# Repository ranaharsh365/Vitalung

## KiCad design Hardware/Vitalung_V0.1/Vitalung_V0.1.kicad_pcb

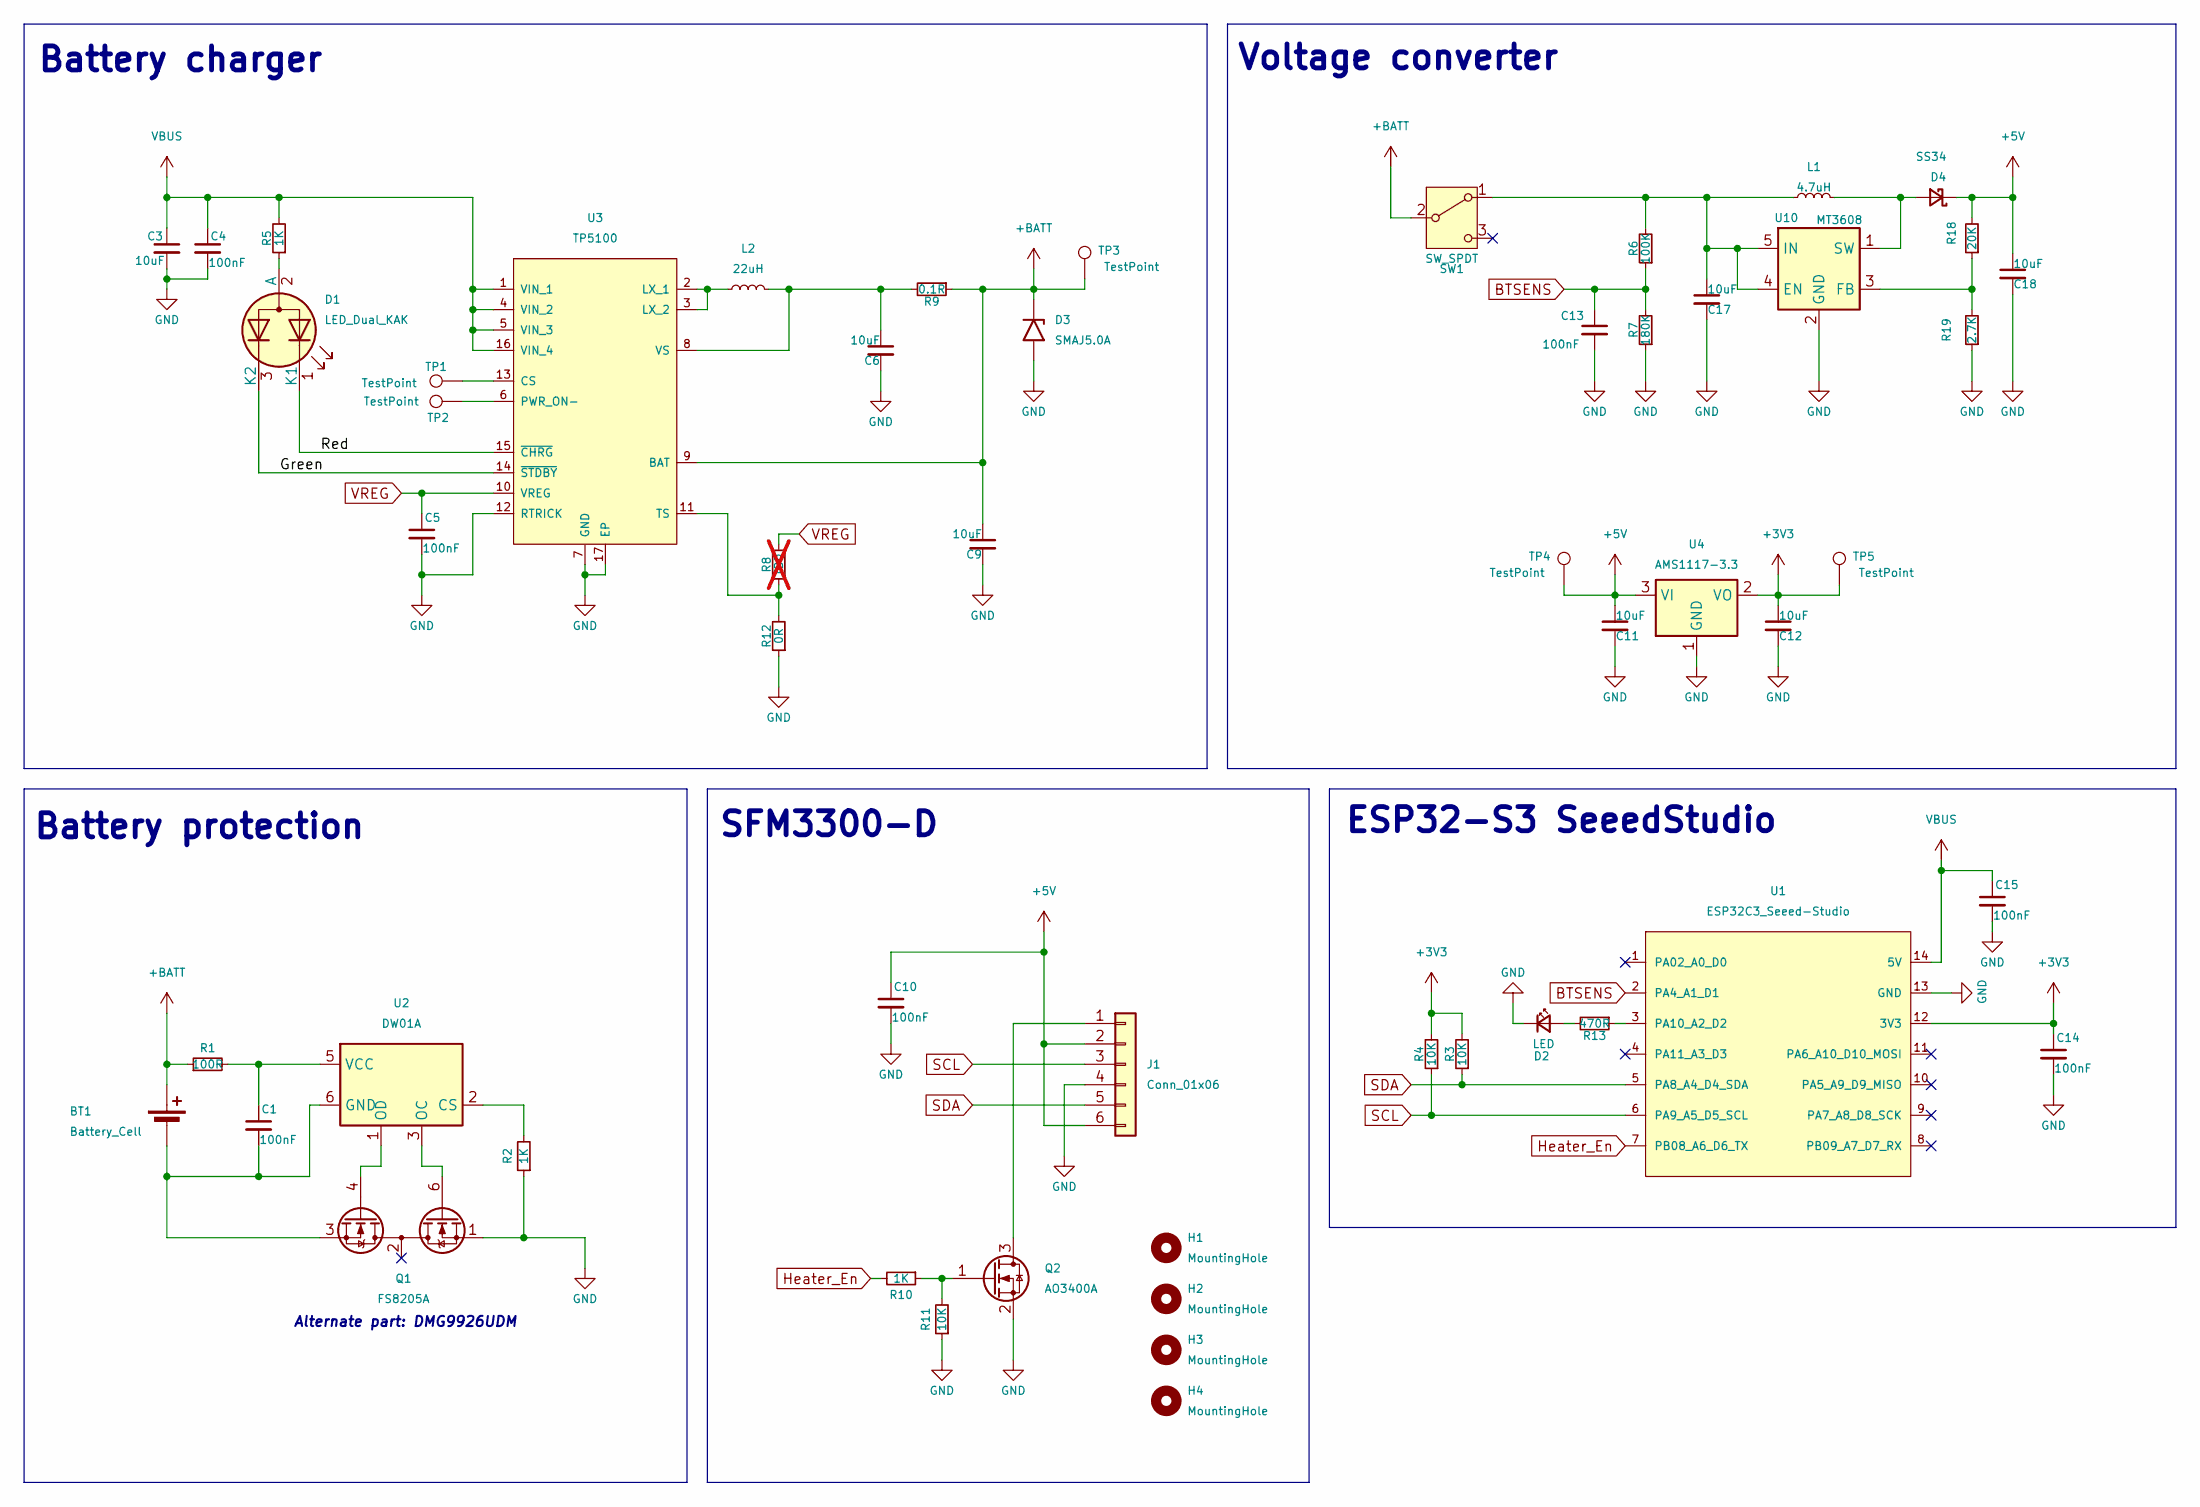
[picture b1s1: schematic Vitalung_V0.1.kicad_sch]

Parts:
BT1: Battery_Cell; BatteryHolder_MPD_BH-18650-PC2
C1, C4, C5, C10, C13, C14, C15: 100nF; C_0603_1608Metric_Pad1.08x0.95mm_HandSolder
C3, C6, C9, C11, C12, C17, C18: 10uF; C_0805_2012Metric_Pad1.18x1.45mm_HandSolder; JLCPCB Part # C96446
D1: LED_Dual_KAK; LED_D3.0mm-3
D2: LED; LED_D3.0mm
D3: SMAJ5.0A; D_SMA
D4: SS34; D_SMA; JLCPCB Part # C8678
H1, H2, H3, H4: MountingHole; MountingHole_2.2mm_M2
J1: Conn_01x06; PinHeader_1x06_P2.54mm_Vertical
L1: 4.7uH; L_Abracon_ASPI-0425; MFR Part no. FXL0420-4R7-M; JLCPCB Part # C167208
L2: 22uH; L_Abracon_ASPI-0630LR
Q1: FS8205A; SOT-23-6
Q2: AO3400A; SOT-23
R1: 100R; R_0603_1608Metric_Pad0.98x0.95mm_HandSolder
R2, R10: 1K; R_0603_1608Metric_Pad0.98x0.95mm_HandSolder
R3, R4: 10K; R_0603_1608Metric_Pad0.98x0.95mm_HandSolder; JLCPCB Part # C4184
R5: 1K; R_0603_1608Metric_Pad0.98x0.95mm_HandSolder; JLCPCB Part # C4184
R6: 100K; R_0603_1608Metric_Pad0.98x0.95mm_HandSolder; JLCPCB Part # C25803
R7: 180K; R_0603_1608Metric_Pad0.98x0.95mm_HandSolder; JLCPCB Part # C123419
R8: TBD; R_0603_1608Metric_Pad0.98x0.95mm_HandSolder; JLCPCB Part # C4184; not fitted
R9: 0.1R; R_0805_2012Metric_Pad1.20x1.40mm_HandSolder; JLCPCB Part # C4184
R11: 10K; R_0603_1608Metric_Pad0.98x0.95mm_HandSolder
R12: 0R; R_0603_1608Metric_Pad0.98x0.95mm_HandSolder; JLCPCB Part # C4184
R13: 470R; R_0603_1608Metric_Pad0.98x0.95mm_HandSolder; JLCPCB Part # C4184
R18: 20K; R_0603_1608Metric_Pad0.98x0.95mm_HandSolder; JLCPCB Part # C4184
R19: 2.7K; R_0603_1608Metric_Pad0.98x0.95mm_HandSolder; JLCPCB Part # C13167
SW1: SW_SPDT; SW_Slide_SPDT_Angled_CK_OS102011MA1Q; JLCPCB Part # C2939726
TP1, TP2, TP3, TP4, TP5: TestPoint; TestPoint_Pad_D1.0mm
U1: ESP32C3_Seeed-Studio; ESP32C3-SeedStudio-SMD-2.54-21X17.8MM
U2: DW01A; SOT-23-6
U3: TP5100; QFN-16-1EP_4x4mm_P0.65mm_EP2.1x2.1mm
U4: AMS1117-3.3; SOT-223-3_TabPin2
U10: MT3608; SOT-23-6; JLCPCB Part # C84817

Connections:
+3V3: C12.1, C14.1, R3.2, R4.2, TP5.1, U1.12 (3V3), U4.2 (VO)
+5V: C10.1, C11.1, C18.1, D4.1 (K), J1.2, J1.6, R18.2, TP4.1, U4.3 (VI)
+BATT: BT1.1 (+), C9.1, D3.1 (A1), R1.1, R9.1, SW1.2 (B), TP3.1, U3.9 (BAT)
/Green: D1.3 (K2), U3.14 (~STDBY)
/Red: D1.1 (K1), U3.15 (~CHRG)
BTSENS: C13.1, R6.1, R7.2, U1.2 (PA4_A1_D1)
GND: C3.2, C4.2, C5.2, C6.2, C9.2, C10.2, C11.2, C12.2, C13.2, C14.2, C15.2, C17.2, C18.2, D2.1 (K), D3.2 (A2), J1.4, Q1.1 (D1), Q2.2 (S), R2.1, R7.1, R11.1, R12.1, R19.1, U1.13 (GND), U3.7 (GND), U3.12 (RTRICK), U3.17 (EP), U4.1 (GND), U10.2 (GND)
Heater_En: R10.2, U1.7 (PB08_A6_D6_TX)
unnamed: BT1.2 (-), C1.2, Q1.3 (S2), U2.6 (GND)
unnamed: D1.2 (A), R5.1
unnamed: D2.2 (A), R13.2
unnamed: D4.2 (A), L1.2, U10.1 (SW)
unnamed: J1.1, Q2.3 (D)
unnamed: Q1.6 (G1), U2.3 (OC)
unnamed: Q1.4 (G2), U2.1 (OD)
unnamed: Q2.1 (G), R10.1, R11.2
unnamed: C17.1, L1.1, R6.2, SW1.1 (A), U10.4 (EN), U10.5 (IN)
unnamed: R13.1, U1.3 (PA10_A2_D2)
unnamed: R2.2, U2.2 (CS)
unnamed: C1.1, R1.2, U2.5 (VCC)
unnamed: TP1.1, U3.13 (CS)
unnamed: L2.1, U3.2 (LX_1), U3.3 (LX_2)
unnamed: TP2.1, U3.6 (PWR_ON-)
unnamed: R8.1, R12.2, U3.11 (TS)
unnamed: C6.1, L2.2, R9.2, U3.8 (VS)
unnamed: R18.1, R19.2, U10.3 (FB)
SCL: J1.3, R4.1, U1.6 (PA9_A5_D5_SCL)
SDA: J1.5, R3.1, U1.5 (PA8_A4_D4_SDA)
VBUS: C3.1, C4.1, C15.1, R5.2, U1.14 (5V), U3.1 (VIN_1), U3.4 (VIN_2), U3.5 (VIN_3), U3.16 (VIN_4)
VREG: C5.1, R8.2, U3.10 (VREG)

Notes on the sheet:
ESP32-S3 SeeedStudio
SFM3300-D
Battery charger
Battery protection
Voltage converter
Alternate part: DMG9926UDM

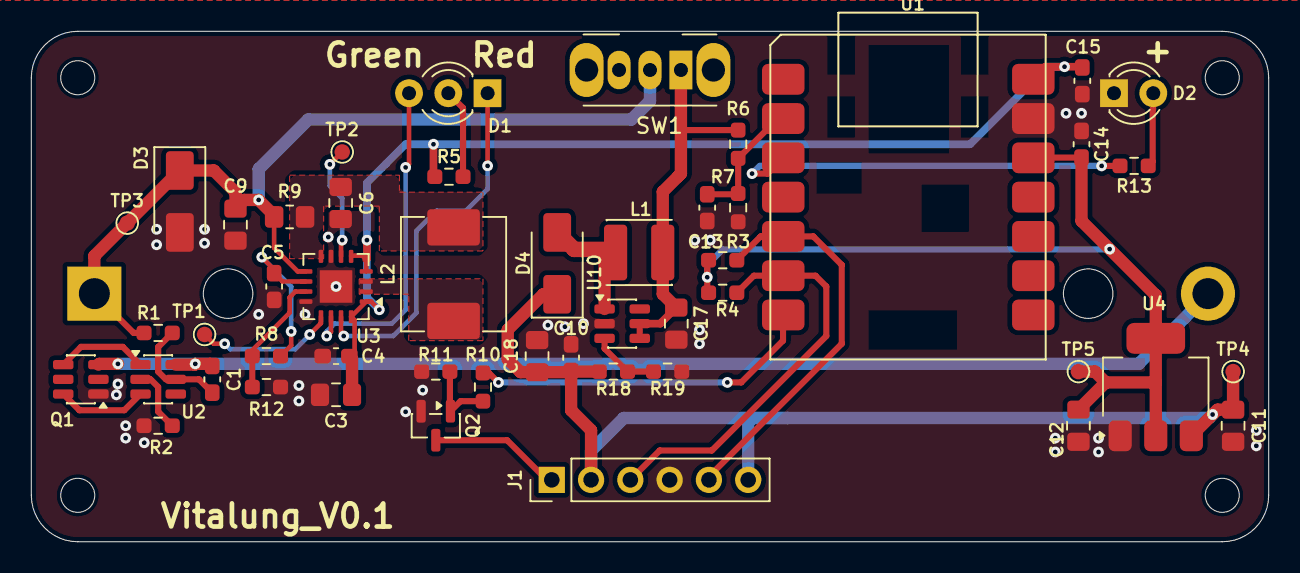
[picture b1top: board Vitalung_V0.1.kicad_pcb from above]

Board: 2 copper layers, 80.0 x 33.0 mm, 54 parts (1 on the bottom side), 30 nets.

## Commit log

2026-01-31 PCB completion
2026-02-03 PCB changes
2026-02-03 PCB DXF change
2026-02-05 Gerber generation
